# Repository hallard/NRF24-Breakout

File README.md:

NRF24L01 Breakout Board Socket
==============================

This is a utility breakout board for connecting NRF24L01 with pinout of 2x4 pins modules. Sometime you need to do prototyping or testing on breadbord, and this board will exactly do this job perfectly!

this breakout have the following features: 

- 10uF Capacitor on VCC line (PTH or SMD)
- Power LED
- Nice pinout reading of exposed pins on PCB silk

If you follow me, you know that I like to use simple NRF24L01 pinout on all my projects, so this mean you can also use this breakout with the following other breakout for HopeRF modules such as:

- RFM12B or RFM69CW with SD and Flash EEP [Breakout Board][2]
- RFM69W with SD and Flash EEP [Breakout Board][3]
- RFM92 RFM95 RFM96 RFM98 Lora modules [Breakout Board][4]

Detailed Description
====================

Nothing fancy, just a matter of wiring, see schematics to view pins exposed.

###Schematic

### Boards  
&nbsp;

You can order the PCB of this board [PCBs.io][6]. PCBs.io give me some reward when you order my designed boards from their site. This is pretty cool because I can use these rewards to order boards for a discounted price and share new designed boards project 

### Received boards 

I'm waiting for boards from [PCBs.io][5]

### Assembled and mounted boards

I'm waiting for boards from [PCBs.io][5]

##License

You can do whatever you like with this design.

##Misc
See news and other projects on my [blog][5] 

[1]: http://hallard.me
[2]: https://github.com/hallard/RFM12B-BreakOut
[3]: https://github.com/hallard/RFM69W-BreakOut
[4]: https://github.com/hallard/Lora-Breakout
[5]: https://PCBs.io
[6]: https://PCBs.io/share/zdP6z

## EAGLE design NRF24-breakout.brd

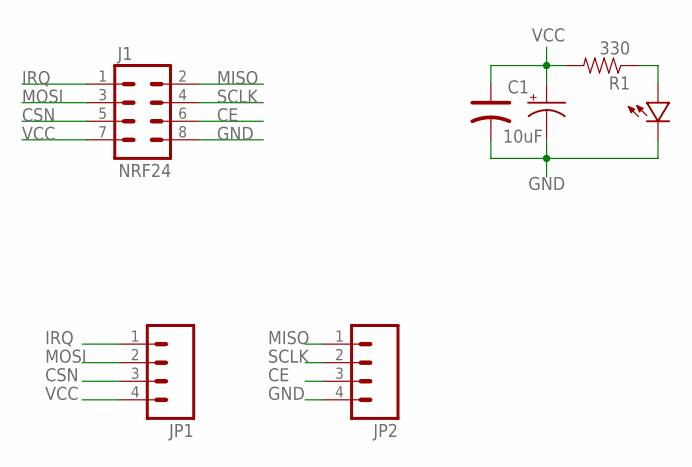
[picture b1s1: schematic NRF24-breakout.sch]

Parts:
C1: 10uF; B45181A
C3: CAP-POLAR-1210; 1210
J1: NRF24; 2X4
JP1, JP2: M04PTH; 1X04
R1: 330; 0805-RES
U$1: LED0805-LARGE; 0805-LED-LARGEPADS

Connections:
CE: J1.6, JP2.3
CSN: J1.5, JP1.3
GND: C1.-, C3.-, J1.8, JP2.4, U$1.MINUS
IRQ: J1.1, JP1.1
MISO: J1.2, JP2.1
MOSI: J1.3, JP1.2
unnamed: R1.1, U$1.PLUS
SCLK: J1.4, JP2.2
VCC: C1.+, C3.+, J1.7, JP1.4, R1.2

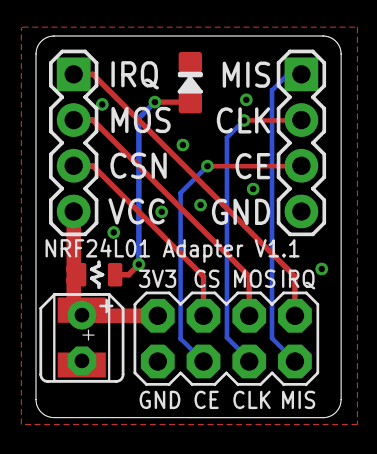
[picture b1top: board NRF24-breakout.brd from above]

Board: 2 copper layers, 17.0 x 21.2 mm, 8 parts (1 on the bottom side), 9 nets.

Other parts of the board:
U$2: LOGO_CH2I_75MM

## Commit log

2016-08-20 :circus_tent: Added .gitattributes & .gitignore files
2016-08-20 Creation
2016-08-20 Link error
2016-08-20 Cosmetic

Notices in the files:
parts and their libraries:
SparkFun-Connectors: Licensing: CC v3.0 Share-Alike You are welcome to use this library for commercial purposes.
SparkFun-Aesthetics: Licensing: Creative Commons ShareAlike 4.0 International - https://creativecommons.org/licenses/by-sa/4.0
